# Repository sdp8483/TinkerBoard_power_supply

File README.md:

Power Board/Shield/Hat/Cape for the Asus Tinker Board

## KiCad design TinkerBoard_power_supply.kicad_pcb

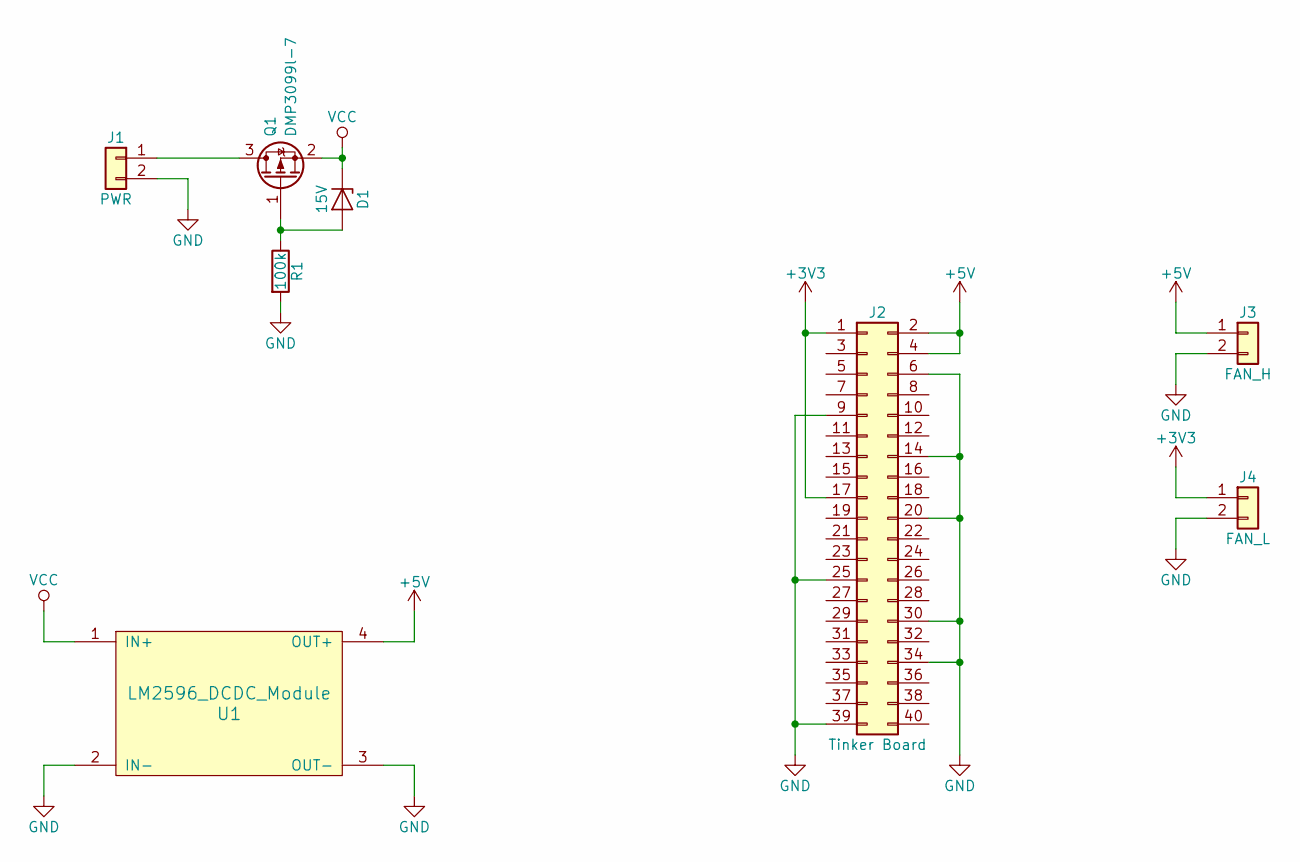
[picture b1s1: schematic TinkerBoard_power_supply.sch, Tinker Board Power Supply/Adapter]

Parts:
D1: 15V; D_SOD-123; Mfg Part Number BZT52C15-7-F
J1: PWR; TerminalBlock_TE_282836-2_1x2_P5.00mm_Horizontal
J2: Tinker Board; Pin_Header_Straight_2x20_Pitch2.54mm
J3: FAN_H; Pin_Header_Straight_1x02_Pitch2.54mm
J4: FAN_L; Pin_Header_Straight_1x02_Pitch2.54mm
Q1: DMP3099l-7; SOT-23; Mfg Part Number DMP3099L-7
R1: 100k; R_1206_HandSoldering; Mfg Part Number NONE
U1: LM2596_DCDC_Module

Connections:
+3V3: J2.1, J2.17, J4.1
+5V: J2.2, J2.4, J3.1, U1.4 (OUT+)
GND: J1.2, J2.6, J2.9, J2.14, J2.20, J2.25, J2.30, J2.34, J2.39, J3.2, J4.2, R1.2, U1.2 (IN-), U1.3 (OUT-)
unnamed: D1.2 (A), Q1.1 (G), R1.1
unnamed: J1.1, Q1.3 (D)
VCC: D1.1 (K), Q1.2 (S), U1.1 (IN+)

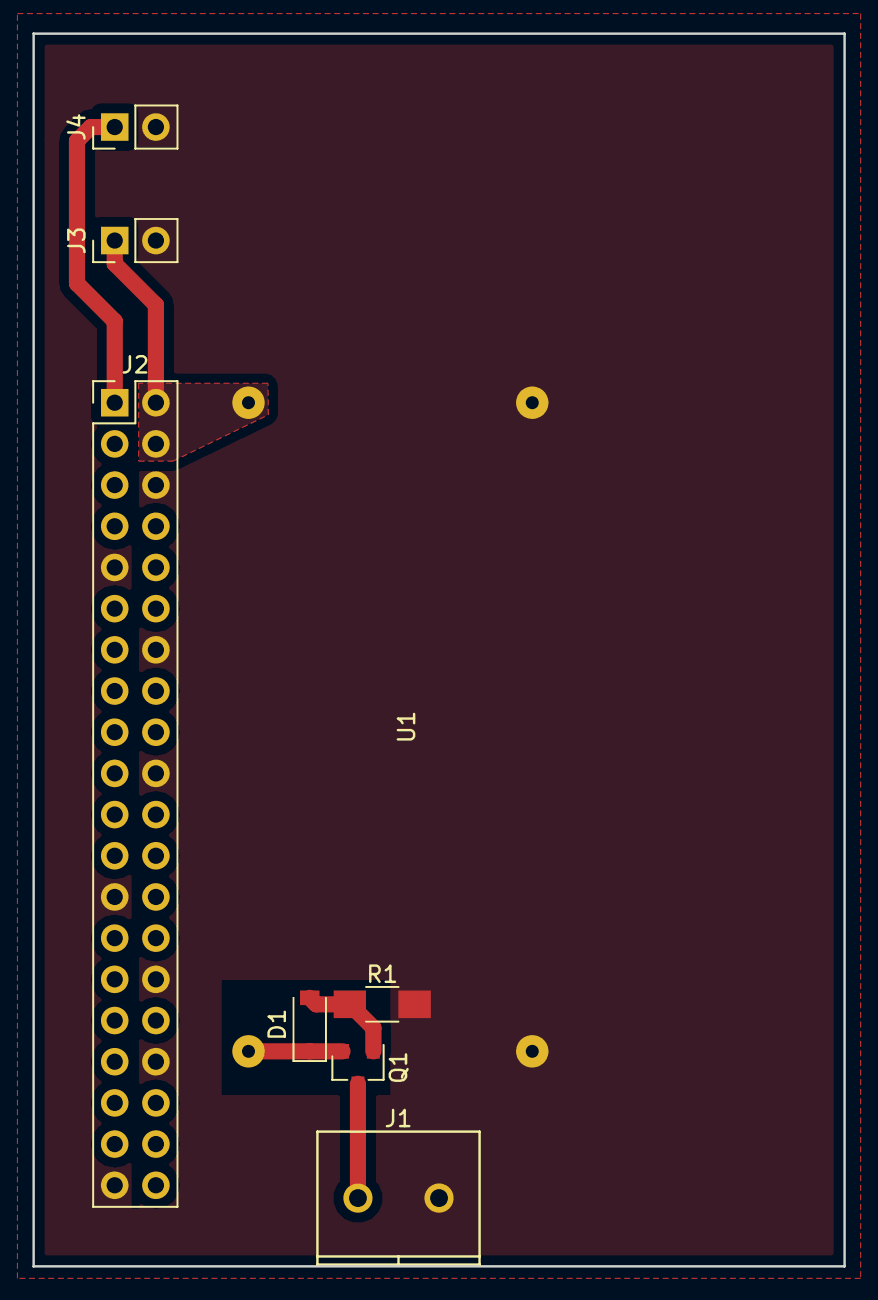
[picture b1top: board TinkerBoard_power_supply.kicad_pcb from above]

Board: 2 copper layers, 50.0 x 76.0 mm, 8 parts (0 on the bottom side), 6 nets.

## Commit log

2018-04-23 Schema Fin
2018-04-24 PCB layout, ready to etch
2018-04-24 image output for etching
